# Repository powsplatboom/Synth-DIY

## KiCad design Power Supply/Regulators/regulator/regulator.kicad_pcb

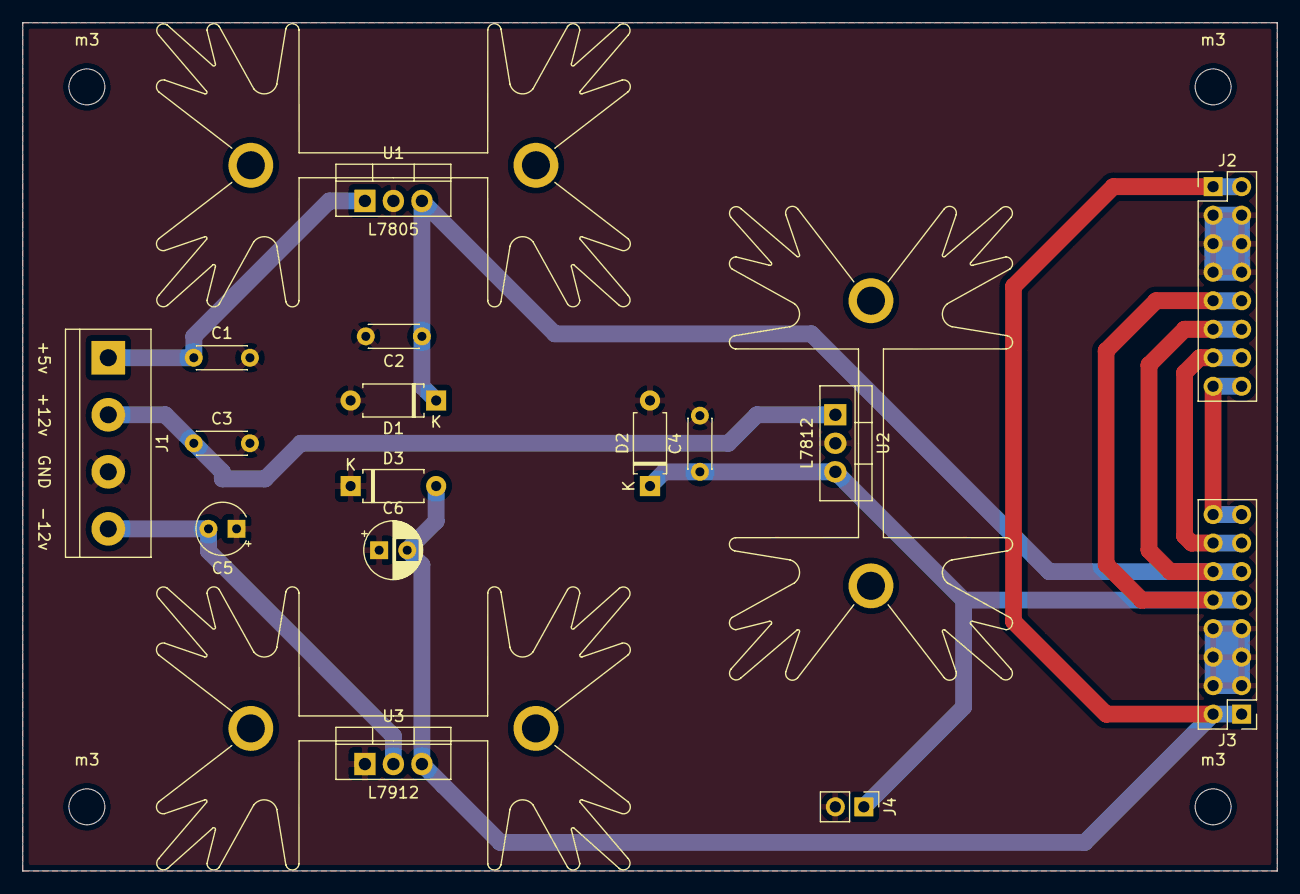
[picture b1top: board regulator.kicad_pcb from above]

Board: 2 copper layers, 111.8 x 75.6 mm, 23 parts (0 on the bottom side), 9 nets.

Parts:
C1, C3: .33uf; C_Disc_D4.3mm_W1.9mm_P5.00mm
C2, C4: .1uf; C_Disc_D4.3mm_W1.9mm_P5.00mm
C5: 2.2uf; CP_Radial_Tantal_D4.5mm_P2.50mm
C6: 1uf; CP_Radial_D5.0mm_P2.50mm
D1, D2, D3: 1N4001; D_A-405_P7.62mm_Horizontal
J1: Conn_01x04_Male; TerminalBlock_bornier-4_P5.08mm
J2, J3: Conn_02x08_Odd_Even; PinHeader_2x08_P2.54mm_Vertical
J4: Conn_01x02_Male; PinHeader_1x02_P2.54mm_Vertical
L7805, L7812, L7912: Heatsink_Fischer_SK129-STS_42x25mm_2xDrill2.5mm
U1: L7805; TO-220-3_Vertical
U2: L7812; TO-220-3_Vertical
U3: L7912; TO-220-3_Vertical
m3, m3#2, m3#3, m3#4: MountingHole_3.2mm_M3

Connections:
unnamed: C1.1, J1.1, U1.1
unnamed: C1.2, C2.2, C3.2, C4.2, C5.1, C6.1, D1.2, D2.2, D3.1, J1.3, J2.3, J2.4, J2.5, J2.6, J2.7, J2.8, J3.3, J3.4, J3.5, J3.6, J3.7, J3.8, J4.2, U1.2, U2.2, U3.1
unnamed: C2.1, D1.1, J2.11, J2.12, J3.11, J3.12, U1.3
unnamed: C3.1, J1.2, U2.1
unnamed: C4.1, D2.1, J2.9, J2.10, J3.9, J3.10, J4.1, U2.3
unnamed: C5.2, J1.4, U3.2
unnamed: C6.2, D3.2, J2.1, J2.2, J3.1, J3.2, U3.3
unnamed: J2.13, J2.14, J3.13, J3.14
unnamed: J2.15, J2.16, J3.15, J3.16

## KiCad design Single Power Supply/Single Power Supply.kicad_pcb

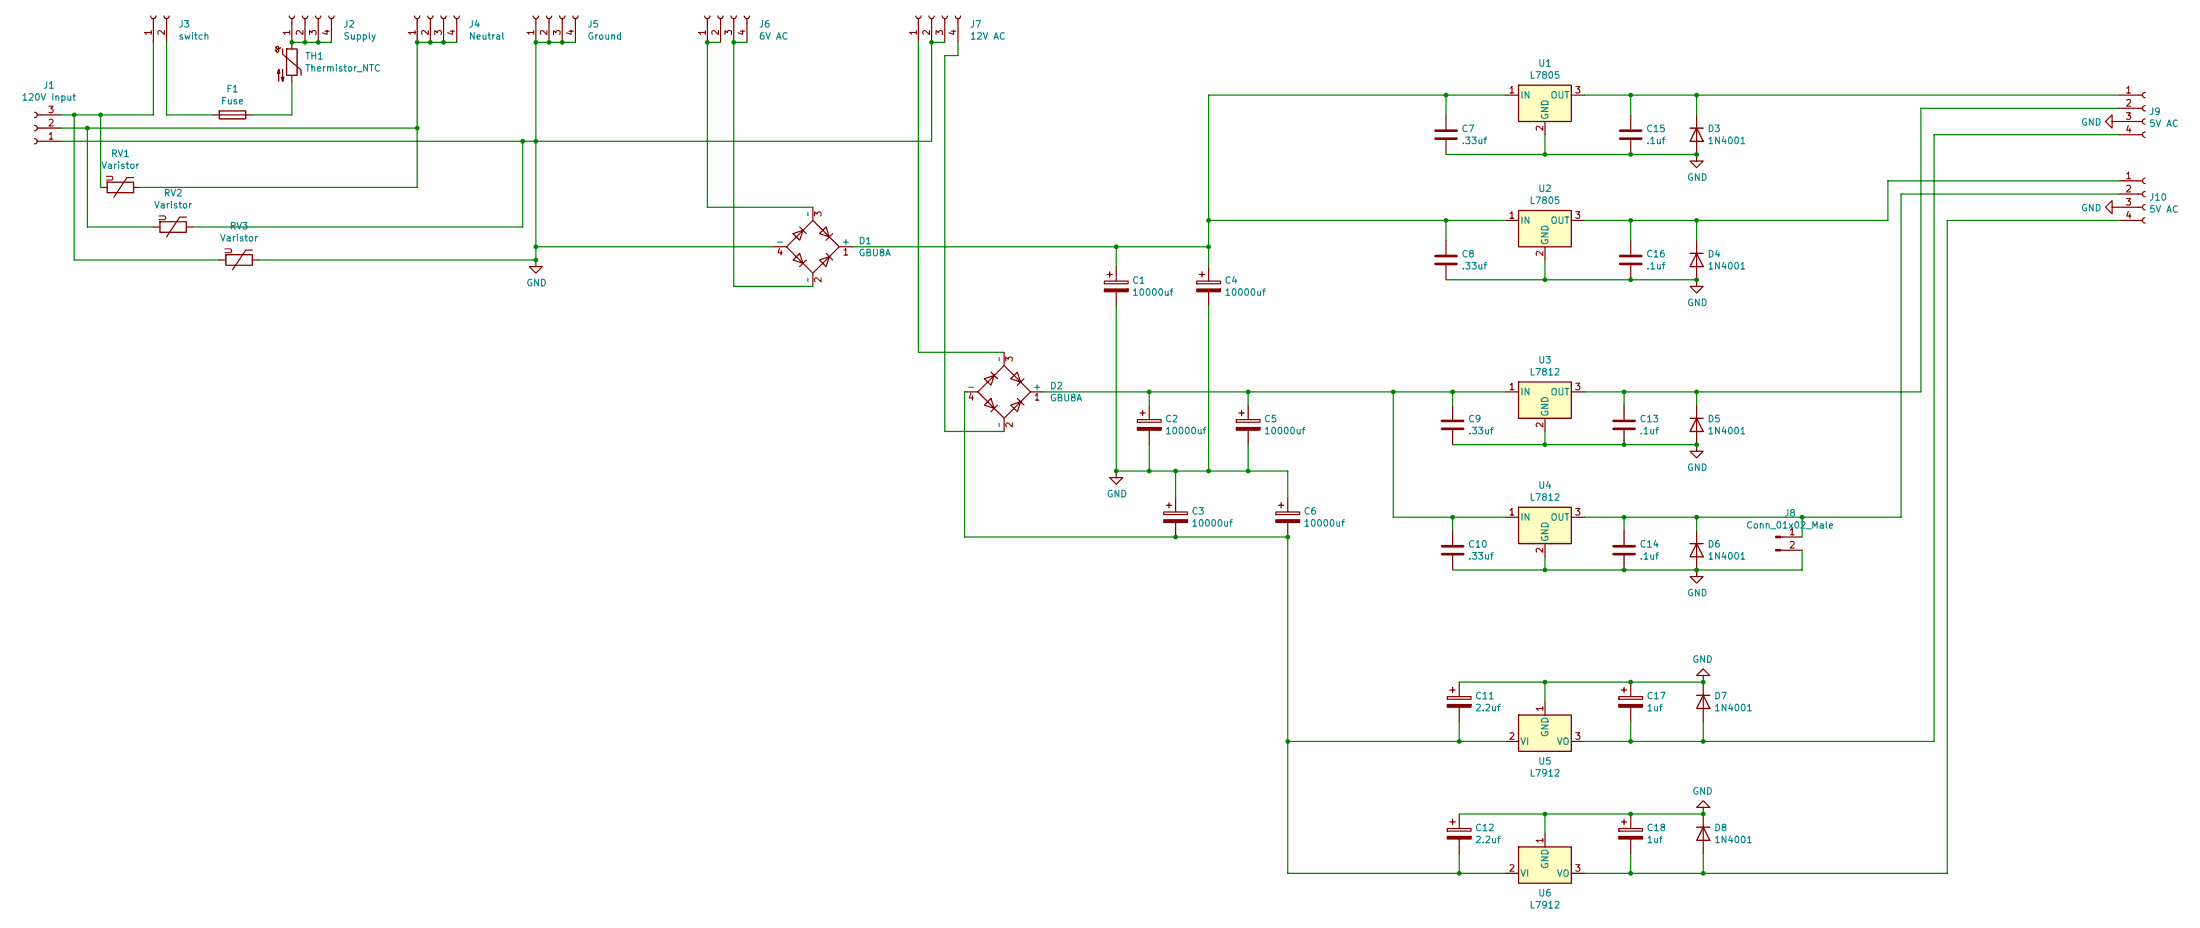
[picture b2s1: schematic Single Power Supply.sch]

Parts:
C1, C2, C3, C4, C5, C6: 10000uf; CP_Radial_D18.0mm_P7.50mm
C7, C8, C9, C10: .33uf; C_Disc_D4.3mm_W1.9mm_P5.00mm
C11, C12: 2.2uf; CP_Radial_D6.3mm_P2.50mm
C13, C14, C15, C16: .1uf; C_Disc_D4.3mm_W1.9mm_P5.00mm
C17, C18: 1uf; CP_Radial_Tantal_D5.0mm_P2.50mm
D1, D2: GBU8A; Diode_Bridge_Vishay_GBU
D3, D4, D5, D6, D7, D8: 1N4001; D_DO-41_SOD81_P10.16mm_Horizontal
F1: Fuse; Fuseholder_Cylinder-5x20mm_Stelvio-Kontek_PTF78_Horizontal_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
J1: 120V Input; TerminalBlock_bornier-3_P5.08mm
J2: Supply; TerminalBlock_bornier-4_P5.08mm
J3: switch; TerminalBlock_bornier-2_P5.08mm
J4: Neutral; TerminalBlock_bornier-4_P5.08mm
J5: Ground; TerminalBlock_bornier-4_P5.08mm
J6: 6V AC; TerminalBlock_bornier-4_P5.08mm
J7: 12V AC; TerminalBlock_bornier-4_P5.08mm
J8: Conn_01x02_Male; JST_EH_B2B-EH-A_1x02_P2.50mm_Vertical
J9, J10: 5V AC; TerminalBlock_bornier-4_P5.08mm
RV1, RV2, RV3: Varistor; RV_Disc_D12mm_W4.2mm_P7.5mm
TH1: Thermistor_NTC; R_Axial_DIN0207_L6.3mm_D2.5mm_P7.62mm_Horizontal
U1, U2: L7805; TO-220-3_Vertical
U3, U4: L7812; TO-220-3_Vertical
U5, U6: L7912; TO-220-3_Vertical

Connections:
GND: C1.2, C2.2, C3.1, C4.2, C5.2, C6.1, C7.2, C8.2, C9.2, C10.2, C11.1, C12.1, C13.2, C14.2, C15.2, C16.2, C17.1, C18.1, D1.4 (-), D3.2 (A), D4.2 (A), D5.2 (A), D6.2 (A), D7.1 (K), D8.1 (K), J1.1, J5.1, J5.2, J5.3, J5.4, J7.2, J7.3, J8.2, J9.3, J10.3, RV2.1, RV3.1, U1.2 (GND), U2.2 (GND), U3.2 (GND), U4.2 (GND), U5.1 (GND), U6.1 (GND)
unnamed: C1.1, C4.1, C7.1, C8.1, D1.1 (+), U1.1 (IN), U2.1 (IN)
unnamed: C2.1, C5.1, C9.1, C10.1, D2.1 (+), U3.1 (IN), U4.1 (IN)
unnamed: C3.2, C6.2, C11.2, C12.2, D2.4 (-), U5.2 (VI), U6.2 (VI)
unnamed: C13.1, D5.1 (K), J9.2, U3.3 (OUT)
unnamed: C14.1, D6.1 (K), J8.1, J10.2, U4.3 (OUT)
unnamed: C15.1, D3.1 (K), J9.1, U1.3 (OUT)
unnamed: C16.1, D4.1 (K), J10.1, U2.3 (OUT)
unnamed: C17.2, D7.2 (A), J9.4, U5.3 (VO)
unnamed: C18.2, D8.2 (A), J10.4, U6.3 (VO)
unnamed: D1.2 (~~), J6.3, J6.4
unnamed: D1.3 (~~), J6.1, J6.2
unnamed: D2.2 (~~), J7.4
unnamed: D2.3 (~~), J7.1
unnamed: F1.1, TH1.2
unnamed: F1.2, J3.2
unnamed: J1.2, J4.1, J4.2, J4.3, J4.4, RV1.1, RV2.2
unnamed: J1.3, J3.1, RV1.2, RV3.2
unnamed: J2.1, J2.2, J2.3, J2.4, TH1.1

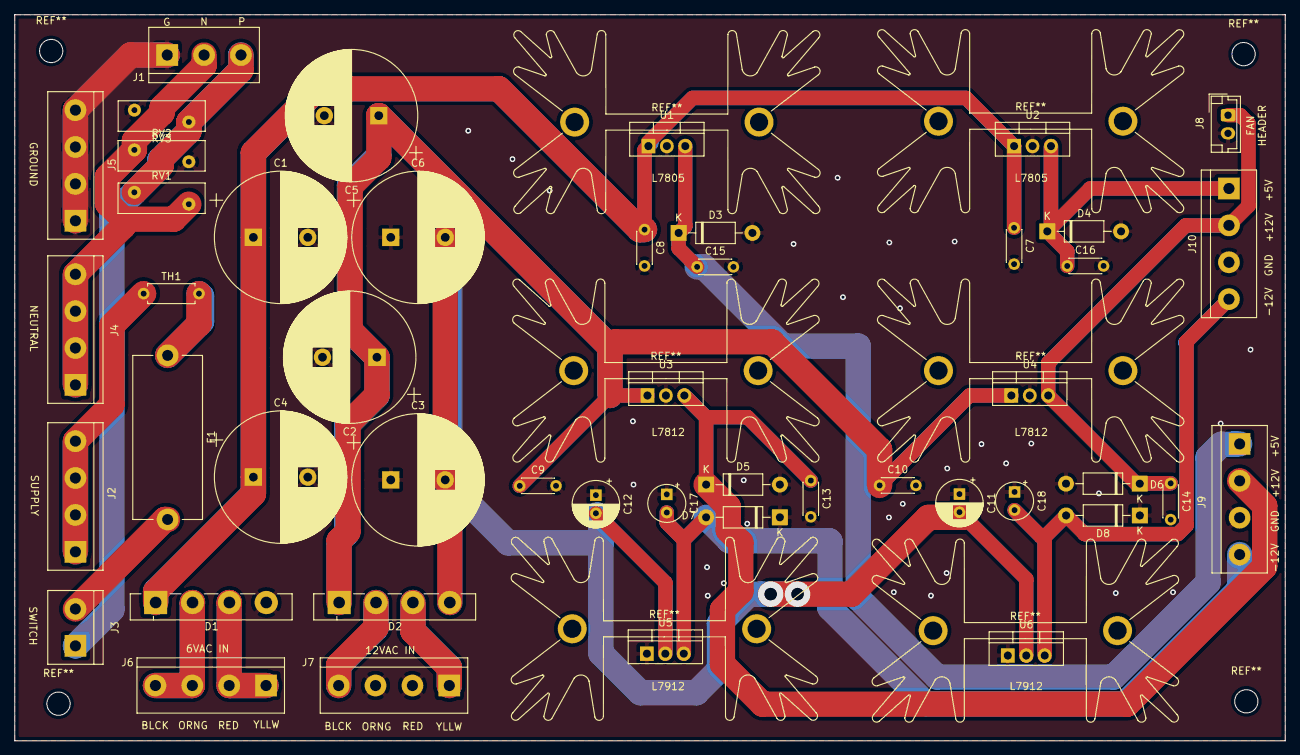
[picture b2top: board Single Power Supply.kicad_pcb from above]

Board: 2 copper layers, 175.0 x 100.0 mm, 47 parts (0 on the bottom side), 19 nets.
